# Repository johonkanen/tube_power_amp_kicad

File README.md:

# Board renders

Rendered by CI from `johonkanen/tube_power_amp_kicad` commit [`66774174bd`](https://github.com/johonkanen/tube_power_amp_kicad/commit/66774174bdc07fa05581503c15b5ecf16376c193) on 2026-11-25 20:45 UTC with 10.0.7.
This branch is force-pushed on every render; do not commit to it.

## tube_power_amp_revb (`rev_b/kicad/tube_power_amp_revb.kicad_pcb`)

Copper layers:
- [B_Cu](tube_power_amp_revb/B_Cu.png)
- [F_Cu](tube_power_amp_revb/F_Cu.png)
- [In1_Cu](tube_power_amp_revb/In1_Cu.png)
- [In2_Cu](tube_power_amp_revb/In2_Cu.png)

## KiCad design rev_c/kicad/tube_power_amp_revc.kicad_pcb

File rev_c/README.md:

# Power amp rev C: schematic (first pass, 2026-11-25)

The minimal redesign of the power amp board after rev B grew too complicated. The plan, the user
decisions and the interface changes are in [PLAN.md](PLAN.md). Rev A (repo root) and rev B
(`rev_b/`) are frozen.

## Where we left off (2026-11-25)

**Done:**
- Plan.
- Schematic (124 parts, ERC 0/0).
- Op amp simulation (all pass; Cf removed).
- Board set up and placed.
- Heater copper. DRC: 0 clearance, 0 parity, silk warnings only.

The board is rebuilt from scratch by `rev_c/tools/layout/build.sh`, which runs placement and then the heater copper. Details are in PLAN.md step 3.

**Next:**
1. **Plate lanes on B:** OT_A along y about 158 to V1 / V2 pin 3; OT_B north from J104 / D105 to y about 150, then east to V3 / V4 pin 3. 6.3 mm clearance, In1 / In2 voided within 4.2 mm, no vias near them.
2. **V_ANODE / V_SCREEN / DRV_A / DRV_B** (450 V class), then the In1 GND plane and the In2 -80 V area under the op amps (PowerPAD thermal vias).
3. **Signals:** tidy the order in the front band, then route with the kicad-agentic-routing skill / KiCadRoutingTools.
4. **Send the interface change list** in PLAN.md to the coordinating session.

A KiCad MCP server is registered in the repo-root `.mcp.json` (`tools/kicad_mcp.sh`); approve it when the session starts.

## State

**Schematic drawn and checked; board placed (first pass), routing next.** Picture: [docs/placement.png](docs/placement.png). The board, generated by `rev_c/tools/layout/make_pcb.py`, has the fixed parts at rev B's positions and the rest parked below it. The layout decisions are in PLAN.md step 3.

- **ERC (KiCad 10.0.7): 0 errors, 0 warnings.**
- **136 symbols on 3 sheets, 124 real parts.** The other 12 are 4 net ties and 8 test pads. For comparison, rev B had 336 and rev A 72.
- Every symbol has a footprint (`lib/footprint_map.csv`), and the BOM is in `bom/tube_power_amp_revc_bom.csv`.

| Sheet | Contents |
|---|---|
| 01 Output stage | As rev B, except the 100n / 630 V HF caps are dropped. 4 octal sockets V1-V4; per tube 220n / 630 V MKP coupling cap, 91k grid leak to BIASn, 5.6k stopper, 1k 5 W flameproof screen resistor, 1 Ω shunt with an S3M across it, Kelvin net tie, 2 test pads. Open-load clamps: RGP02-20E from GND to each plate, 2x P6KE350CA from each plate to the centre tap. Tabs J101-J104, drive header J105 (Mini-Fit Jr 2x3) |
| 02 Bias | J201 (-80 V, BIAS_RTN on GNDD), 10R fusible resistor, S1G reverse clamp, 100 µF + 100 nF. ADR4525 2.5 V reference. DAC7578 (TSSOP: resets to zero; ADDR0 = VDD → **0x4A**). Per tube one **OPA462** (180 V, SO-8 PowerPAD, +15 V / -80 V): 10k / 115k + 330n input, Rf / Rg = 280k / 10k 0.1 % to VREF2V5 (no cap across Rf: sim P1), 1k / 1 µF to BIASn. **Vout = 26.7 · Vdac − 70.0 V**: power-on (DAC 0) = −70 V cold, full scale −3.3 V |
| 03 Sense, ribbons | ADS1115 ×3. **0x48**: V1 and V2; **0x49**: V3 and V4, both differential across the shunt with 1k + 1k and 1 µF. **0x4B**: -80 V (536k / 10k offset divider to VREF2V5), +15 V / 6, VREF2V5 direct, +5 V / 2. J501 (W14-b): +5 V, +15 V, GNDD only. J502 (W15-b): I2C, pins 6-9 not connected. 100 Ω I2C crossings, 4.7k pull-ups, soft tie 10 Ω ‖ 100 nF, bulk caps |

## Checked against the datasheets

The datasheet PDFs were read for this pass:

**OPA462 (SBOS803A)**
- Pins: 1 E/D Com, 2 −IN, 3 +IN, 4 V−, 5 flag, 6 OUT, 7 V+, 8 E/D. The PowerPAD is on V−.
- Supply ±6 V to ±90 V.
- Iq 3.2 mA typical, 3.7 mA max.
- Input common mode (V−)+1 to (V+)−3 V.
- E/D at least 0.65 V above E/D Com means enabled, with E/D at most 7 V above E/D Com. E/D Com must sit between V− and (V+)−6 V while the supply is below 106 V.

**OPA454 (SBOS391B).** It allows 100 V recommended and 120 V absolute between its rails, too close to the 95-97 V here. That is why the OPA462 was chosen.

**DAC7578.**
- TSSOP-16 addresses: ADDR0 = GND 0x48, VDD 0x4A, float 0x4C.
- The TSSOP versions reset to zero scale at power-on.
- Pinout as in KiCad's symbol.

**ADS1115 (SBAS444E)**
- Addresses: GND 0x48, VDD 0x49, SDA 0x4A, SCL 0x4B.
- Analog inputs GND−0.3 to VDD+0.3 V, ±10 mA. Digital inputs up to 5.5 V.
- Differential input impedance 710 kΩ at ±0.256 V. That is why the input resistors are 1k, not 10k.

## Open checks before the layout

- **OPA462 details still to read:** its output swing (the datasheet's electrical table), and the DDA0008J exposed pad compared with KiCad's `TI_SO-PowerPAD-8`.
- ~~**Stability**~~: done 2026-11-25. ngspice with TI's OPA462 model, rev_c/sim/opamp/results.md: DC, stability (81° with no Cf), drive coupling, power-up, -80 V loss and dissipation all pass or are informational. Note: the 1 µF / 100 V 0805 keeps about 0.25 µF at 70 V (1 kHz ripple on BIASn 0.29 V peak); consider 1206 at ordering.
- ~~**Inrush** of the 100 µF through the 10R fusible resistor at plug-in~~: closed 2026-11-25. The board is never hot-plugged (user), so the 100 µF charges as the PSU's -80 V ramps up.
- **Interface changes:** the list in PLAN.md goes to the coordinating session (tube_amplifier_kicad interfaces.md).

## Build

```
python3 rev_c/tools/make_lib.py          # lib/tube_power_amp_revc.kicad_sym: stock symbols (flattened) + OPA462
python3 rev_c/tools/make_project.py      # project, root sheet, empty sub-sheets
python3 rev_c/tools/make_footprints.py   # board-local footprints copied from rev B, fp-lib-table
python3 rev_c/tools/sheets/draw_all.py   # draws the 3 sheets, writes lib/footprint_map.csv and bom/*.csv
cd rev_c/kicad && ../../tools/p2k/bin/kicad-cli sch erc --severity-all tube_power_amp_revc.kicad_sch
cd - && tools/p2k/bin/kipy rev_c/tools/layout/make_pcb.py   # board: outline, holes, rules, fixed parts, the rest parked
```

The sheets are generated: edit `tools/sheets/draw_all.py`, not the `.kicad_sch` files, until the
draft is frozen. The drawing style is netlist-first, as in rev B.

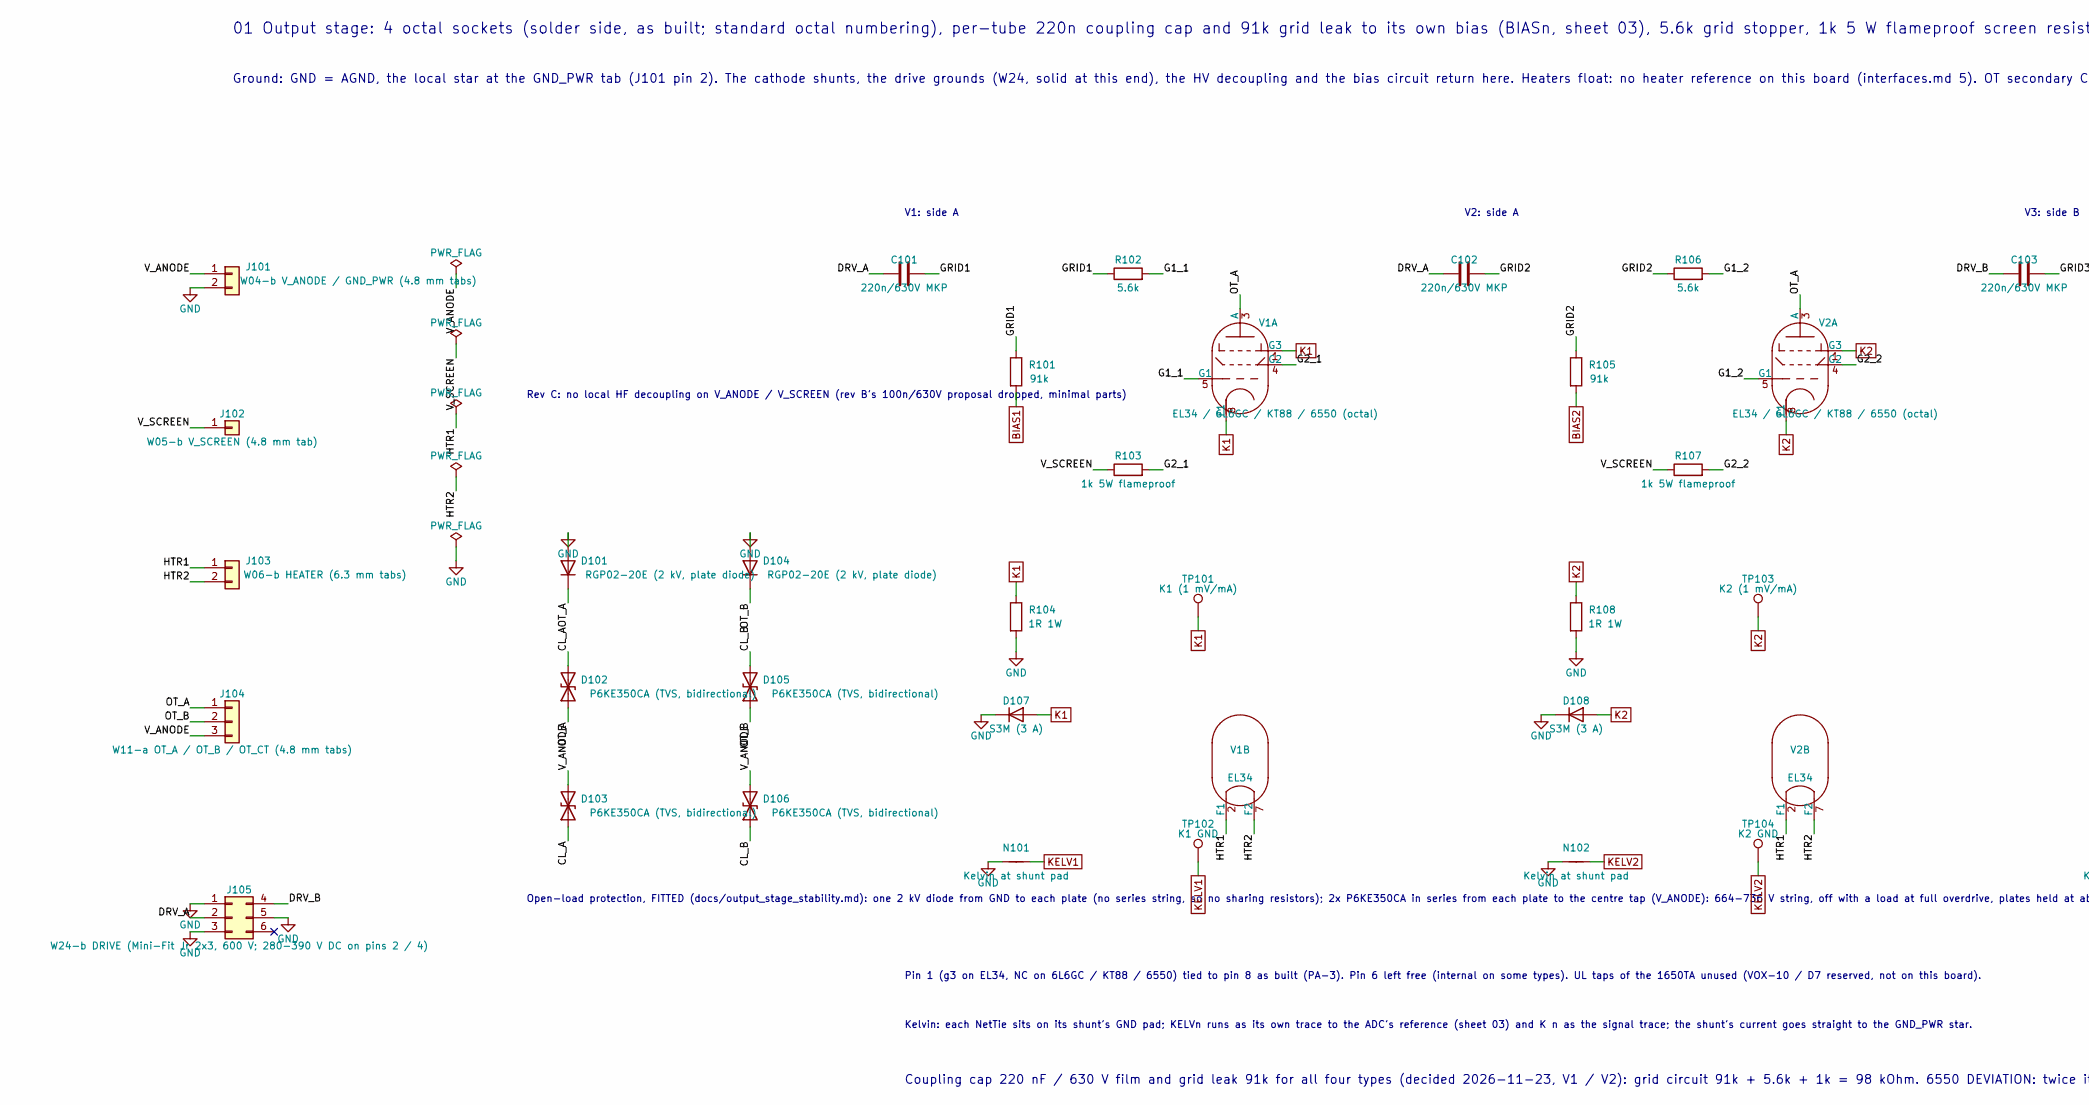
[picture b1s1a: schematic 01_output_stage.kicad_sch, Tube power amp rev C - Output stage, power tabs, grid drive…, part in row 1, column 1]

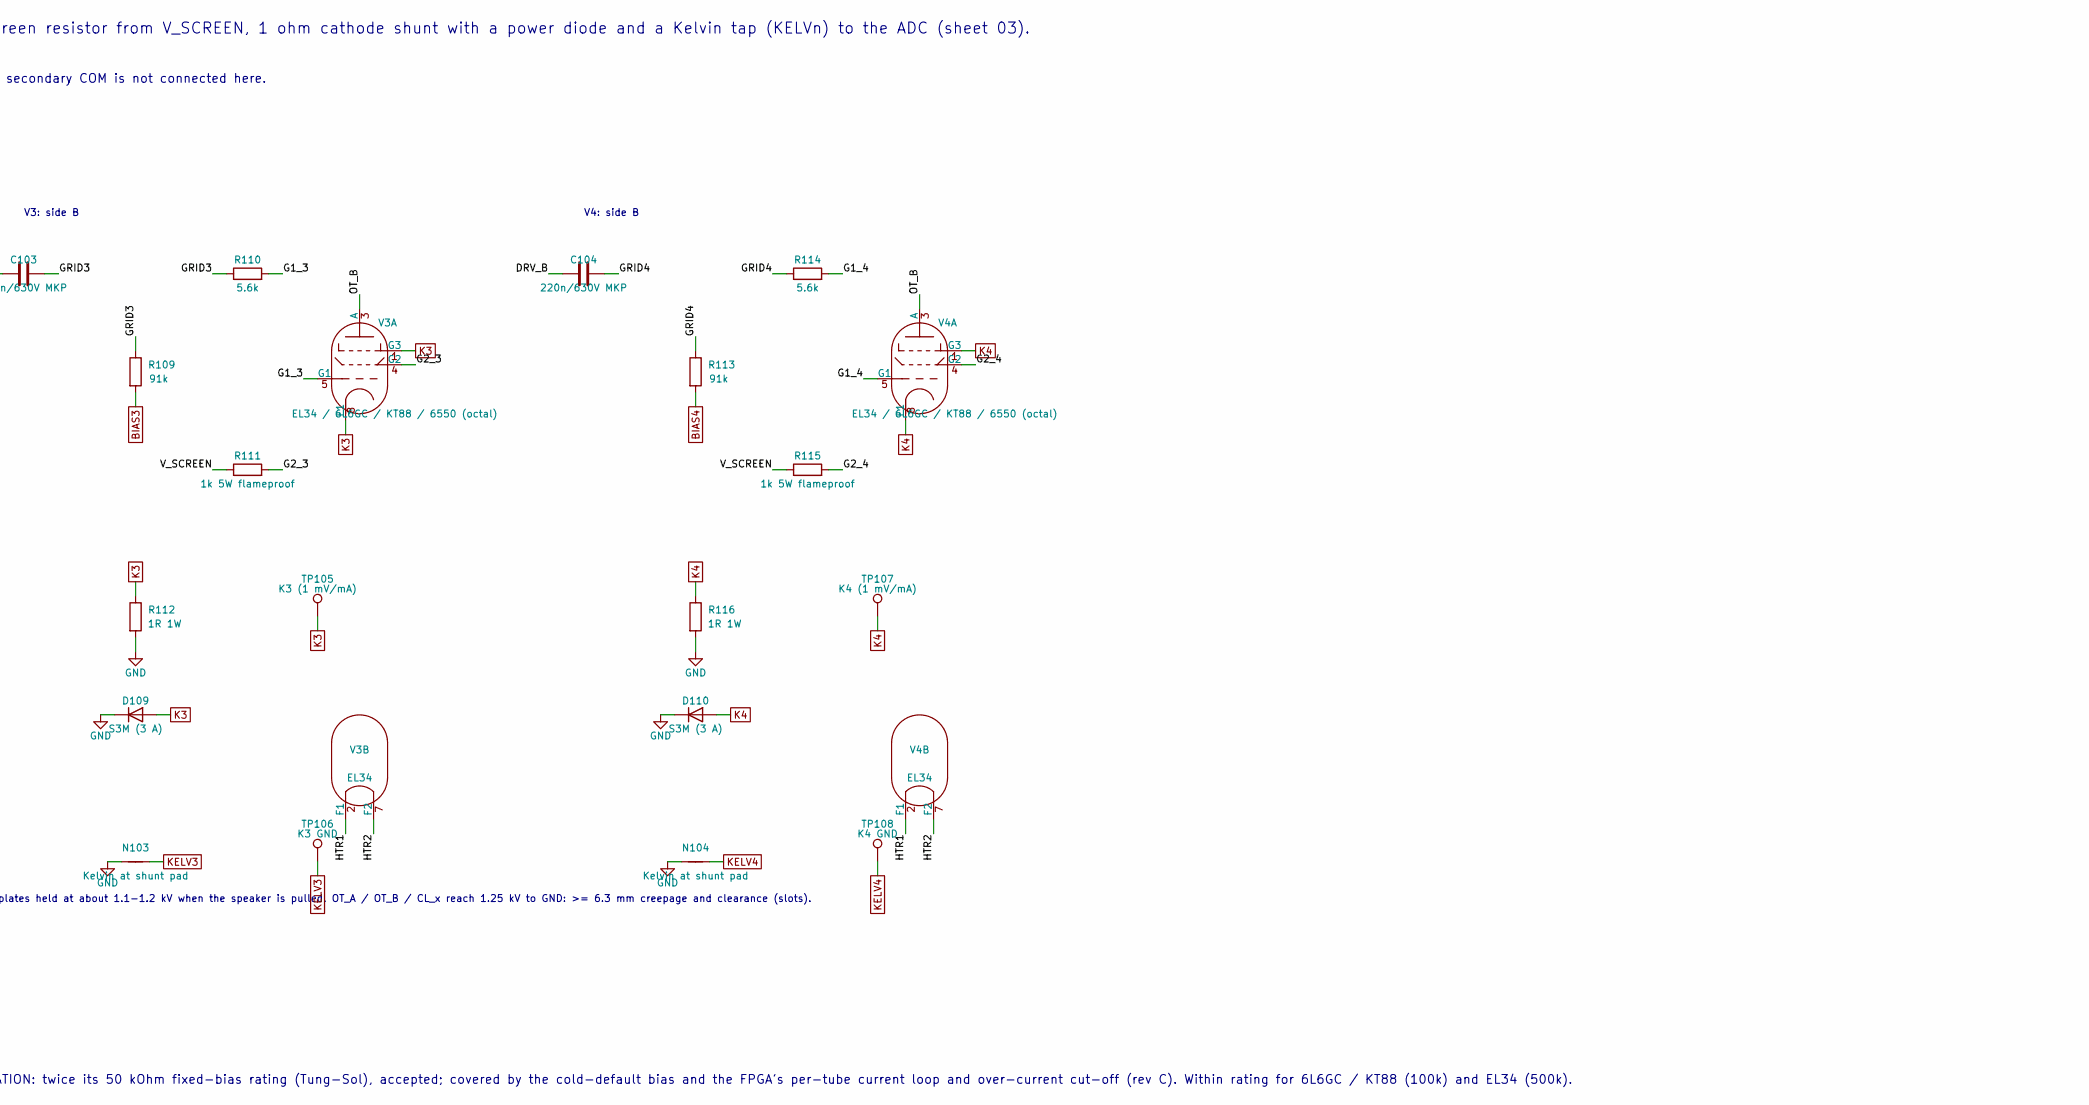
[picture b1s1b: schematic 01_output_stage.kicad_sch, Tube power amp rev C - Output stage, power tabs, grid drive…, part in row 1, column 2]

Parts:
C101, C102, C103, C104: 220n/630V MKP; C_Rect_L26.5mm_W8.5mm_P22.50mm_MKS4
D101, D104: RGP02-20E (2 kV, plate diode); D_DO-41_SOD81_P10.16mm_Horizontal
D102, D103, D105, D106: P6KE350CA (TVS, bidirectional); D_DO-15_P10.16mm_Horizontal
D107, D108, D109, D110: S3M (3 A); D_SMC
J101: W04-b V_ANODE / GND_PWR (4.8 mm tabs); BladeTab_4.8mm_x2_P10.20mm_Inline
J102: W05-b V_SCREEN (4.8 mm tab); BladeTab_4.8mm_x1
J103: W06-b HEATER (6.3 mm tabs); BladeTab_6.3mm_x2_P11.50mm
J104: W11-a OT_A / OT_B / OT_CT (4.8 mm tabs); BladeTab_4.8mm_x3_OT
J105: W24-b DRIVE (Mini-Fit Jr 2x3, 600 V; 280-390 V DC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; Molex_Mini-Fit_Jr_5566-06A_2x03_P4.20mm_Vertical
N101, N102, N103, N104: Kelvin at shunt pad; NetTie-2_SMD_Pad0.5mm
R101, R105, R109, R113: 91k; R_2512_6332Metric
R102, R106, R110, R114: 5.6k; R_1206_3216Metric
R103, R107, R115: 1k 5W flameproof; R_Axial_Power_L25.0mm_W6.4mm_P27.94mm
R104, R108, R112, R116: 1R 1W; R_2512_6332Metric
R111: 1k 5W flameproof; R_Axial_Power_L25.0mm_W9.0mm_P10.16mm_Vertical_Tight
TP101: K1 (1 mV/mA); TestPoint_Pad_D2.0mm
TP102: K1 GND; TestPoint_Pad_D2.0mm
TP103: K2 (1 mV/mA); TestPoint_Pad_D2.0mm
TP104: K2 GND; TestPoint_Pad_D2.0mm
TP105: K3 (1 mV/mA); TestPoint_Pad_D2.0mm
TP106: K3 GND; TestPoint_Pad_D2.0mm
TP107: K4 (1 mV/mA); TestPoint_Pad_D2.0mm
TP108: K4 GND; TestPoint_Pad_D2.0mm
V1, V2, V3, V4: EL34 / 6L6GC / KT88 / 6550 (octal); Valve_Octal_Belton_PCD17.20mm

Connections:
/01 Output stage, power tabs, grid drive, open-load clamps/CL_A: D102.2 (A2), D103.1 (A1)
/01 Output stage, power tabs, grid drive, open-load clamps/CL_B: D105.2 (A2), D106.1 (A1)
/01 Output stage, power tabs, grid drive, open-load clamps/DRV_A: C101.1, C102.1, J105.2
/01 Output stage, power tabs, grid drive, open-load clamps/DRV_B: C103.1, C104.1, J105.4
/01 Output stage, power tabs, grid drive, open-load clamps/G1_1: R102.2, V1.5 (G1)
/01 Output stage, power tabs, grid drive, open-load clamps/G1_2: R106.2, V2.5 (G1)
/01 Output stage, power tabs, grid drive, open-load clamps/G1_3: R110.2, V3.5 (G1)
/01 Output stage, power tabs, grid drive, open-load clamps/G1_4: R114.2, V4.5 (G1)
/01 Output stage, power tabs, grid drive, open-load clamps/G2_1: R103.2, V1.4 (G2)
/01 Output stage, power tabs, grid drive, open-load clamps/G2_2: R107.2, V2.4 (G2)
/01 Output stage, power tabs, grid drive, open-load clamps/G2_3: R111.2, V3.4 (G2)
/01 Output stage, power tabs, grid drive, open-load clamps/G2_4: R115.2, V4.4 (G2)
/01 Output stage, power tabs, grid drive, open-load clamps/GRID1: C101.2, R101.1, R102.1
/01 Output stage, power tabs, grid drive, open-load clamps/GRID2: C102.2, R105.1, R106.1
/01 Output stage, power tabs, grid drive, open-load clamps/GRID3: C103.2, R109.1, R110.1
/01 Output stage, power tabs, grid drive, open-load clamps/GRID4: C104.2, R113.1, R114.1
/01 Output stage, power tabs, grid drive, open-load clamps/HTR1: J103.1, V1.2 (F1), V2.2 (F1), V3.2 (F1), V4.2 (F1)
/01 Output stage, power tabs, grid drive, open-load clamps/HTR2: J103.2, V1.7 (F2), V2.7 (F2), V3.7 (F2), V4.7 (F2)
/01 Output stage, power tabs, grid drive, open-load clamps/OT_A: D101.1 (K), D102.1 (A1), J104.1, V1.3 (A), V2.3 (A)
/01 Output stage, power tabs, grid drive, open-load clamps/OT_B: D104.1 (K), D105.1 (A1), J104.2, V3.3 (A), V4.3 (A)
/01 Output stage, power tabs, grid drive, open-load clamps/V_ANODE: D103.2 (A2), D106.2 (A2), J101.1, J104.3
/01 Output stage, power tabs, grid drive, open-load clamps/V_SCREEN: J102.1, R103.1, R107.1, R111.1, R115.1
BIAS1: R101.2; also elsewhere on the board
BIAS2: R105.2; also elsewhere on the board
BIAS3: R109.2; also elsewhere on the board
BIAS4: R113.2; also elsewhere on the board
GND: D101.2 (A), D104.2 (A), D107.1 (K), D108.1 (K), D109.1 (K), D110.1 (K), J101.2, J105.1, J105.3, J105.5, N101.1, N102.1, N103.1, N104.1, R104.2, R108.2, R112.2, R116.2; also elsewhere on the board
K1: D107.2 (A), R104.1, TP101.1, V1.1 (G3), V1.8 (F1); also elsewhere on the board
K2: D108.2 (A), R108.1, TP103.1, V2.1 (G3), V2.8 (F1); also elsewhere on the board
K3: D109.2 (A), R112.1, TP105.1, V3.1 (G3), V3.8 (F1); also elsewhere on the board
K4: D110.2 (A), R116.1, TP107.1, V4.1 (G3), V4.8 (F1); also elsewhere on the board
KELV1: N101.2, TP102.1; also elsewhere on the board
KELV2: N102.2, TP104.1; also elsewhere on the board
KELV3: N103.2, TP106.1; also elsewhere on the board
KELV4: N104.2, TP108.1; also elsewhere on the board

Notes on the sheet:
01 Output stage: 4 octal sockets (solder side, as built; standard octal numbering), per-tube 220n coupling cap and 91k grid leak to its own bias (BIASn, sheet 03), 5.6k grid stopper, 1k 5 W flameproof screen resistor from V_SCREEN, 1 ohm cathode shunt with a power diode and a Kelvin tap (KELVn) to 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
Coupling cap 220 nF / 630 V film and grid leak 91k for all four types (decided 2026-11-23, V1 / V2): grid circuit 91k + 5.6k + 1k = 98 kOhm. 6550 DEVIATION: twice its 50 kOhm fixed-bias rating (Tung-Sol), accepted; covered by the cold-default bias and the FPGA's per-tube current loop and over-curre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
Ground: GND = AGND, the local star at the GND_PWR tab (J101 pin 2). The cathode shunts, the drive grounds (W24, solid at this end), the HV decoupling and the bias circuit return here. Heaters float: no heater reference on this board (interfaces.md 5). OT secondary COM is not connected here.
Rev C: no local HF decoupling on V_ANODE / V_SCREEN (rev B's 100n/630V proposal dropped, minimal parts)
Open-load protection, FITTED (docs/output_stage_stability.md): one 2 kV diode from GND to each plate (no series string, so no sharing resistors); 2x P6KE350CA in series from each plate to the centre tap (V_ANODE): 664-736 V string, off with a load at full overdrive, plates held at about 1.1-1.2 kV 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
V1: side A
V2: side A
V3: side B
V4: side B
Pin 1 (g3 on EL34, NC on 6L6GC / KT88 / 6550) tied to pin 8 as built (PA-3). Pin 6 left free (internal on some types). UL taps of the 1650TA unused (VOX-10 / D7 reserved, not on this board).
Kelvin: each NetTie sits on its shunt's GND pad; KELVn runs as its own trace to the ADC's reference (sheet 03) and K n as the signal trace; the shunt's current goes straight to the GND_PWR star.

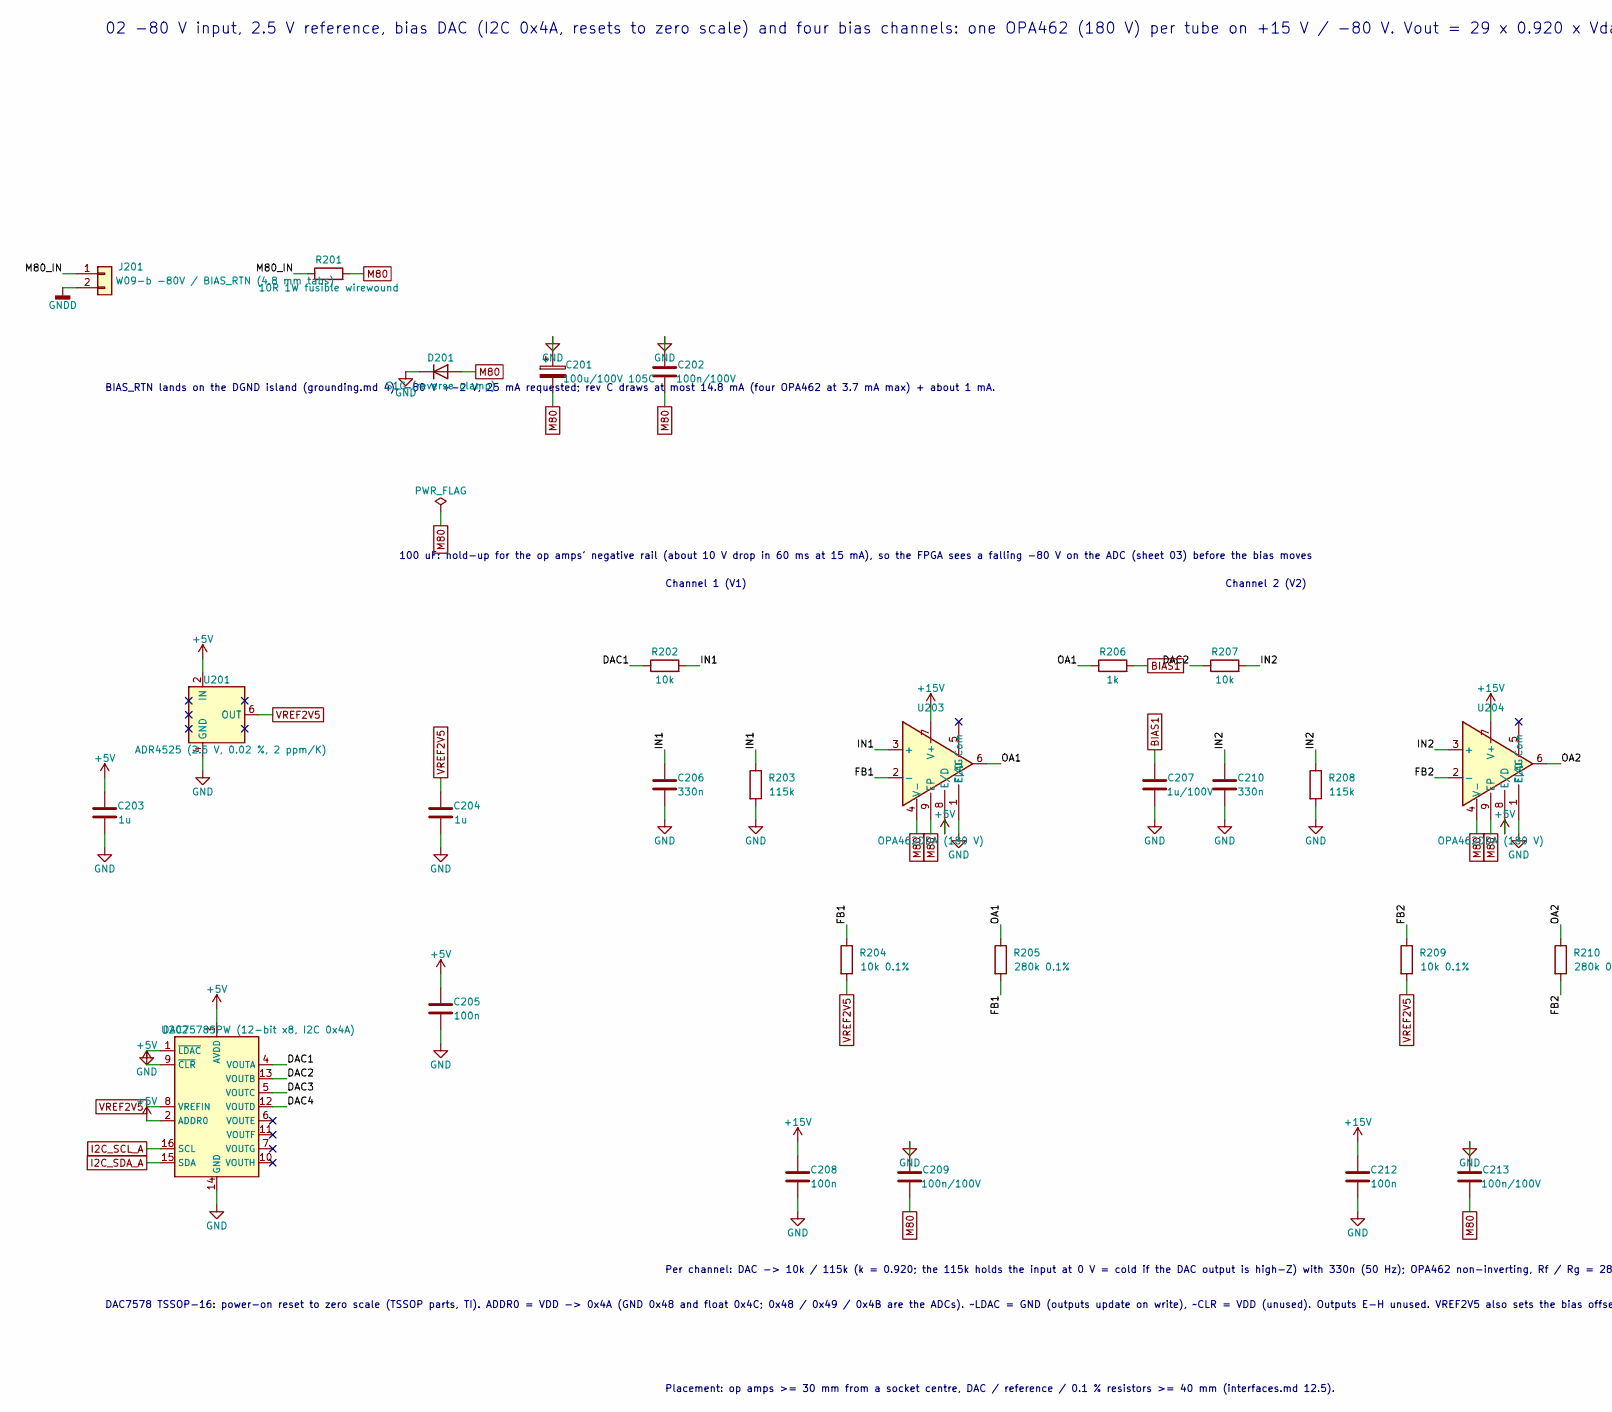
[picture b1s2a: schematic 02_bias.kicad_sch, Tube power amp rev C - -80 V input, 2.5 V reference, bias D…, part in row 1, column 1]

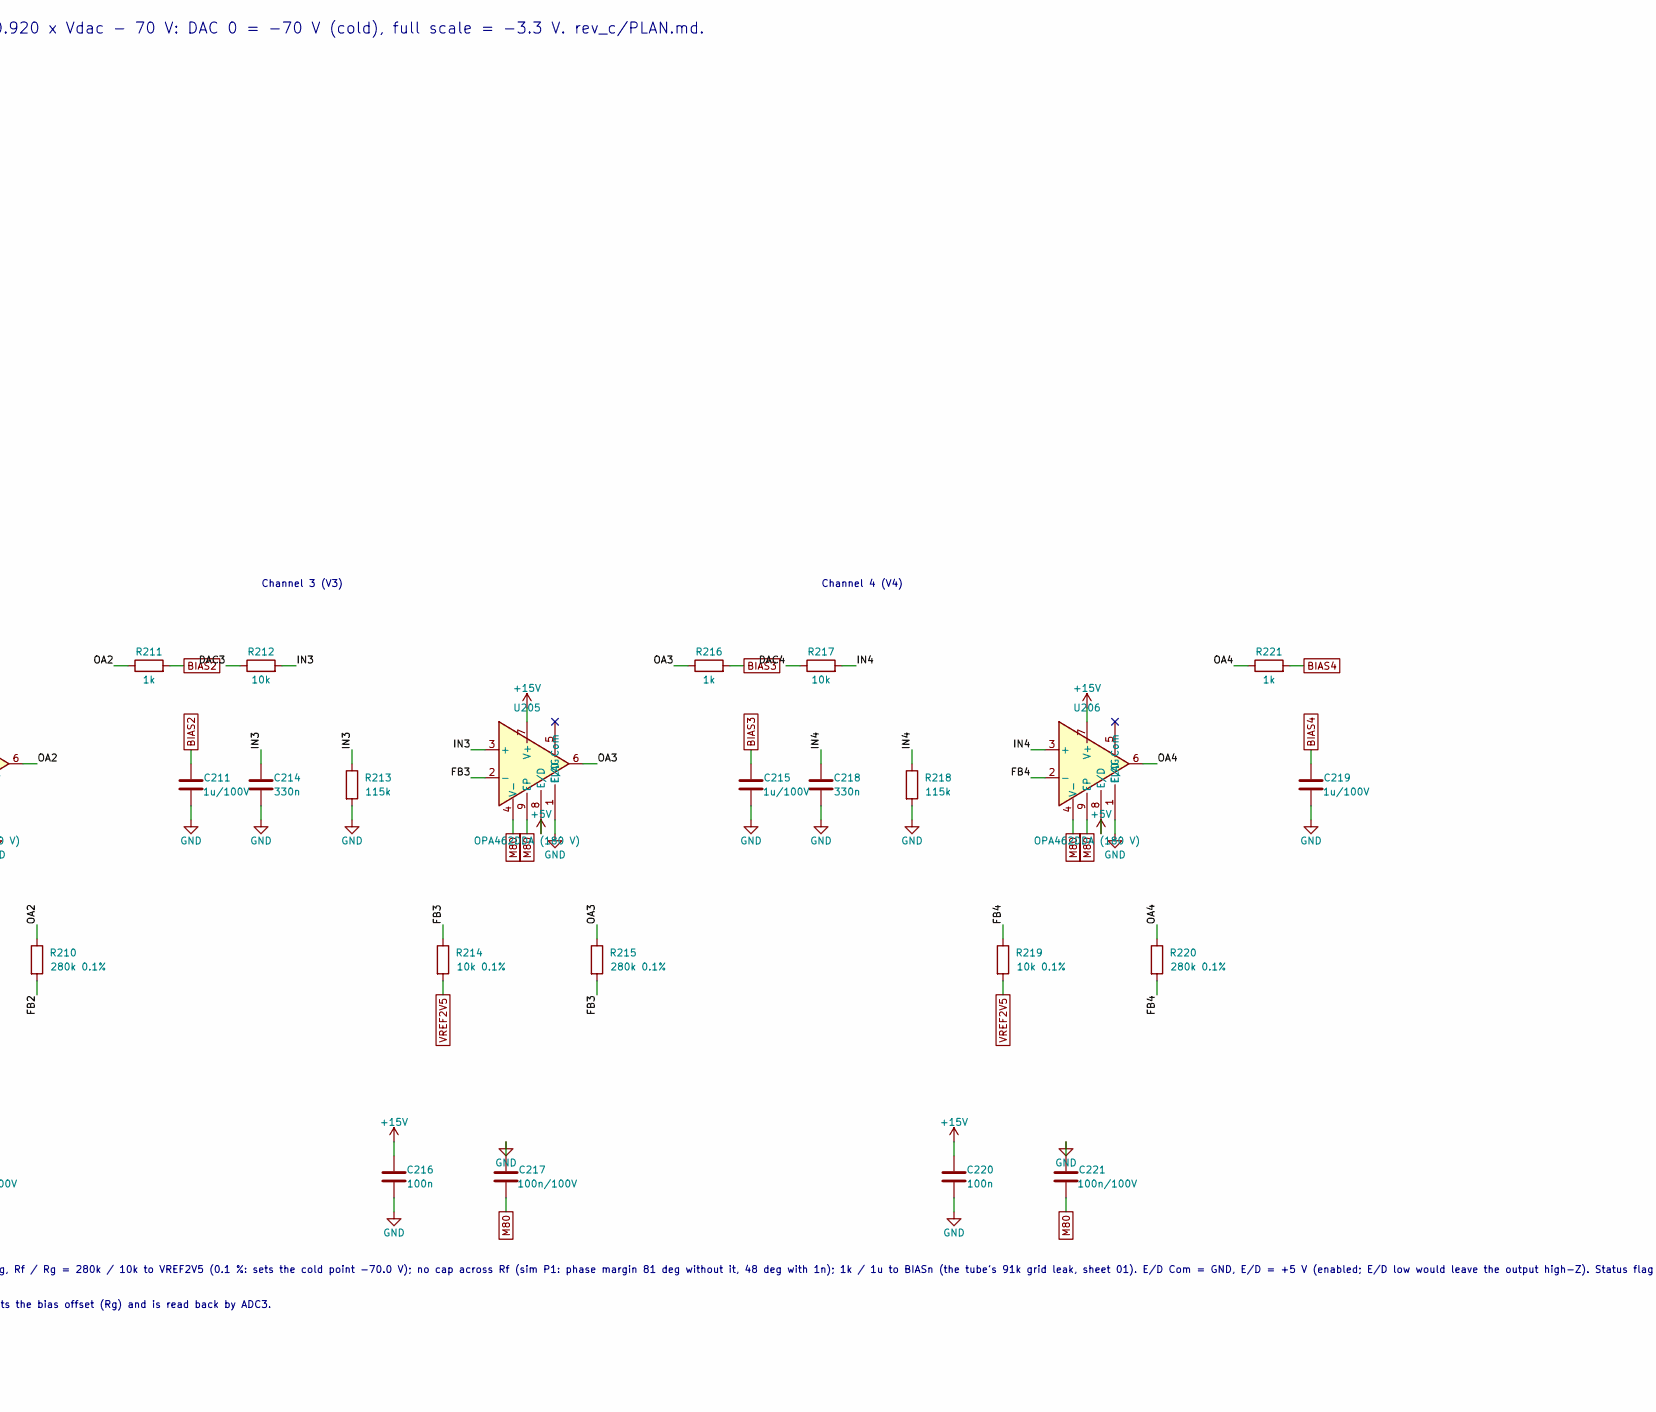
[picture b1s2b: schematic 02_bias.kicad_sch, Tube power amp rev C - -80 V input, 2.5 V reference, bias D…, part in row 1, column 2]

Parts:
C201: 100u/100V 105C; CP_Radial_D10.0mm_P5.00mm
C202, C209, C213, C217, C221: 100n/100V; C_0805_2012Metric
C203, C204: 1u; C_0603_1608Metric
C205, C208, C212, C216, C220: 100n; C_0603_1608Metric
C206, C210, C214, C218: 330n; C_0805_2012Metric
C207, C211, C215, C219: 1u/100V; C_0805_2012Metric
D201: S1G (reverse clamp); D_SMA
J201: W09-b -80V / BIAS_RTN (4.8 mm tabs); BladeTab_4.8mm_x2_P9.50mm
R201: 10R 1W fusible wirewound; R_Axial_DIN0309_L9.0mm_D3.2mm_P12.70mm_Horizontal
R202, R207, R212, R217: 10k; R_0603_1608Metric
R203, R208, R213, R218: 115k; R_0603_1608Metric
R204, R209, R214, R219: 10k 0.1%; R_1206_3216Metric
R205, R210, R215, R220: 280k 0.1%; R_1206_3216Metric
R206, R211, R216, R221: 1k; R_0603_1608Metric
U201: ADR4525 (2.5 V, 0.02 %, 2 ppm/K); SOIC-8_3.9x4.9mm_P1.27mm
U202: DAC7578SPW (12-bit x8, I2C 0x4A); TSSOP-16_4.4x5mm_P0.65mm
U203, U204, U205, U206: OPA462DDA (180 V); TI_SO-PowerPAD-8_ThermalVias

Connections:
+5V: C203.1, C205.1, U201.2 (IN), U202.2 (ADDR0), U202.3 (AVDD), U202.9 (~CLR), U203.8 (E/D), U204.8 (E/D), U205.8 (E/D), U206.8 (E/D); also elsewhere on the board
+15V: C208.1, C212.1, C216.1, C220.1, U203.7 (V+), U204.7 (V+), U205.7 (V+), U206.7 (V+); also elsewhere on the board
/02 -80 V input, 2.5 V reference, bias DAC, four HV op amp bias channels/DAC1: R202.1, U202.4 (VOUTA)
/02 -80 V input, 2.5 V reference, bias DAC, four HV op amp bias channels/DAC2: R207.1, U202.13 (VOUTB)
/02 -80 V input, 2.5 V reference, bias DAC, four HV op amp bias channels/DAC3: R212.1, U202.5 (VOUTC)
/02 -80 V input, 2.5 V reference, bias DAC, four HV op amp bias channels/DAC4: R217.1, U202.12 (VOUTD)
/02 -80 V input, 2.5 V reference, bias DAC, four HV op amp bias channels/FB1: R204.1, R205.2, U203.2 (-)
/02 -80 V input, 2.5 V reference, bias DAC, four HV op amp bias channels/FB2: R209.1, R210.2, U204.2 (-)
/02 -80 V input, 2.5 V reference, bias DAC, four HV op amp bias channels/FB3: R214.1, R215.2, U205.2 (-)
/02 -80 V input, 2.5 V reference, bias DAC, four HV op amp bias channels/FB4: R219.1, R220.2, U206.2 (-)
/02 -80 V input, 2.5 V reference, bias DAC, four HV op amp bias channels/IN1: C206.1, R202.2, R203.1, U203.3 (+)
/02 -80 V input, 2.5 V reference, bias DAC, four HV op amp bias channels/IN2: C210.1, R207.2, R208.1, U204.3 (+)
/02 -80 V input, 2.5 V reference, bias DAC, four HV op amp bias channels/IN3: C214.1, R212.2, R213.1, U205.3 (+)
/02 -80 V input, 2.5 V reference, bias DAC, four HV op amp bias channels/IN4: C218.1, R217.2, R218.1, U206.3 (+)
/02 -80 V input, 2.5 V reference, bias DAC, four HV op amp bias channels/M80_IN: J201.1, R201.1
/02 -80 V input, 2.5 V reference, bias DAC, four HV op amp bias channels/OA1: R205.1, R206.1, U203.6
/02 -80 V input, 2.5 V reference, bias DAC, four HV op amp bias channels/OA2: R210.1, R211.1, U204.6
/02 -80 V input, 2.5 V reference, bias DAC, four HV op amp bias channels/OA3: R215.1, R216.1, U205.6
/02 -80 V input, 2.5 V reference, bias DAC, four HV op amp bias channels/OA4: R220.1, R221.1, U206.6
BIAS1: C207.1, R206.2; also elsewhere on the board
BIAS2: C211.1, R211.2; also elsewhere on the board
BIAS3: C215.1, R216.2; also elsewhere on the board
BIAS4: C219.1, R221.2; also elsewhere on the board
GND: C201.1, C202.1, C203.2, C204.2, C205.2, C206.2, C207.2, C208.2, C209.1, C210.2, C211.2, C212.2, C213.1, C214.2, C215.2, C216.2, C217.1, C218.2, C219.2, C220.2, C221.1, D201.1 (K), R203.2, R208.2, R213.2, R218.2, U201.4 (GND), U202.1 (~LDAC), U202.14 (GND), U203.1 (E/D Com), U204.1 (E/D Com), U205.1 (E/D Com), U206.1 (E/D Com); also elsewhere on the board
GNDD: J201.2; also elsewhere on the board
I2C_SCL_A: U202.16 (SCL); also elsewhere on the board
I2C_SDA_A: U202.15 (SDA); also elsewhere on the board
M80: C201.2, C202.2, C209.2, C213.2, C217.2, C221.2, D201.2 (A), R201.2, U203.4 (V-), U203.9 (EP), U204.4 (V-), U204.9 (EP), U205.4 (V-), U205.9 (EP), U206.4 (V-), U206.9 (EP); also elsewhere on the board
VREF2V5: C204.1, R204.2, R209.2, R214.2, R219.2, U201.6 (OUT), U202.8 (VREFIN); also elsewhere on the board

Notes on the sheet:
02 -80 V input, 2.5 V reference, bias DAC (I2C 0x4A, resets to zero scale) and four bias channels: one OPA462 (180 V) per tube on +15 V / -80 V. Vout = 29 x 0.920 x Vdac - 70 V: DAC 0 = -70 V (cold), full scale = -3.3 V. rev_c/PLAN.md.
BIAS_RTN lands on the DGND island (grounding.md 4). -80 V +-2 V, 25 mA requested; rev C draws at most 14.8 mA (four OPA462 at 3.7 mA max) + about 1 mA.
100 uF: hold-up for the op amps' negative rail (about 10 V drop in 60 ms at 15 mA), so the FPGA sees a falling -80 V on the ADC (sheet 03) before the bias moves
DAC7578 TSSOP-16: power-on reset to zero scale (TSSOP parts, TI). ADDR0 = VDD -> 0x4A (GND 0x48 and float 0x4C; 0x48 / 0x49 / 0x4B are the ADCs). ~LDAC = GND (outputs update on write), ~CLR = VDD (unused). Outputs E-H unused. VREF2V5 also sets the bias offset (Rg) and is read back by ADC3.
Channel 1 (V1)
Channel 2 (V2)
Channel 3 (V3)
Channel 4 (V4)
Per channel: DAC -> 10k / 115k (k = 0.920; the 115k holds the input at 0 V = cold if the DAC output is high-Z) with 330n (50 Hz); OPA462 non-inverting, Rf / Rg = 280k / 10k to VREF2V5 (0.1 %: sets the cold point -70.0 V); no cap across Rf (sim P1: phase margin 81 deg without it, 48 deg with 1n); 1k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
Placement: op amps >= 30 mm from a socket centre, DAC / reference / 0.1 % resistors >= 40 mm (interfaces.md 12.5).
